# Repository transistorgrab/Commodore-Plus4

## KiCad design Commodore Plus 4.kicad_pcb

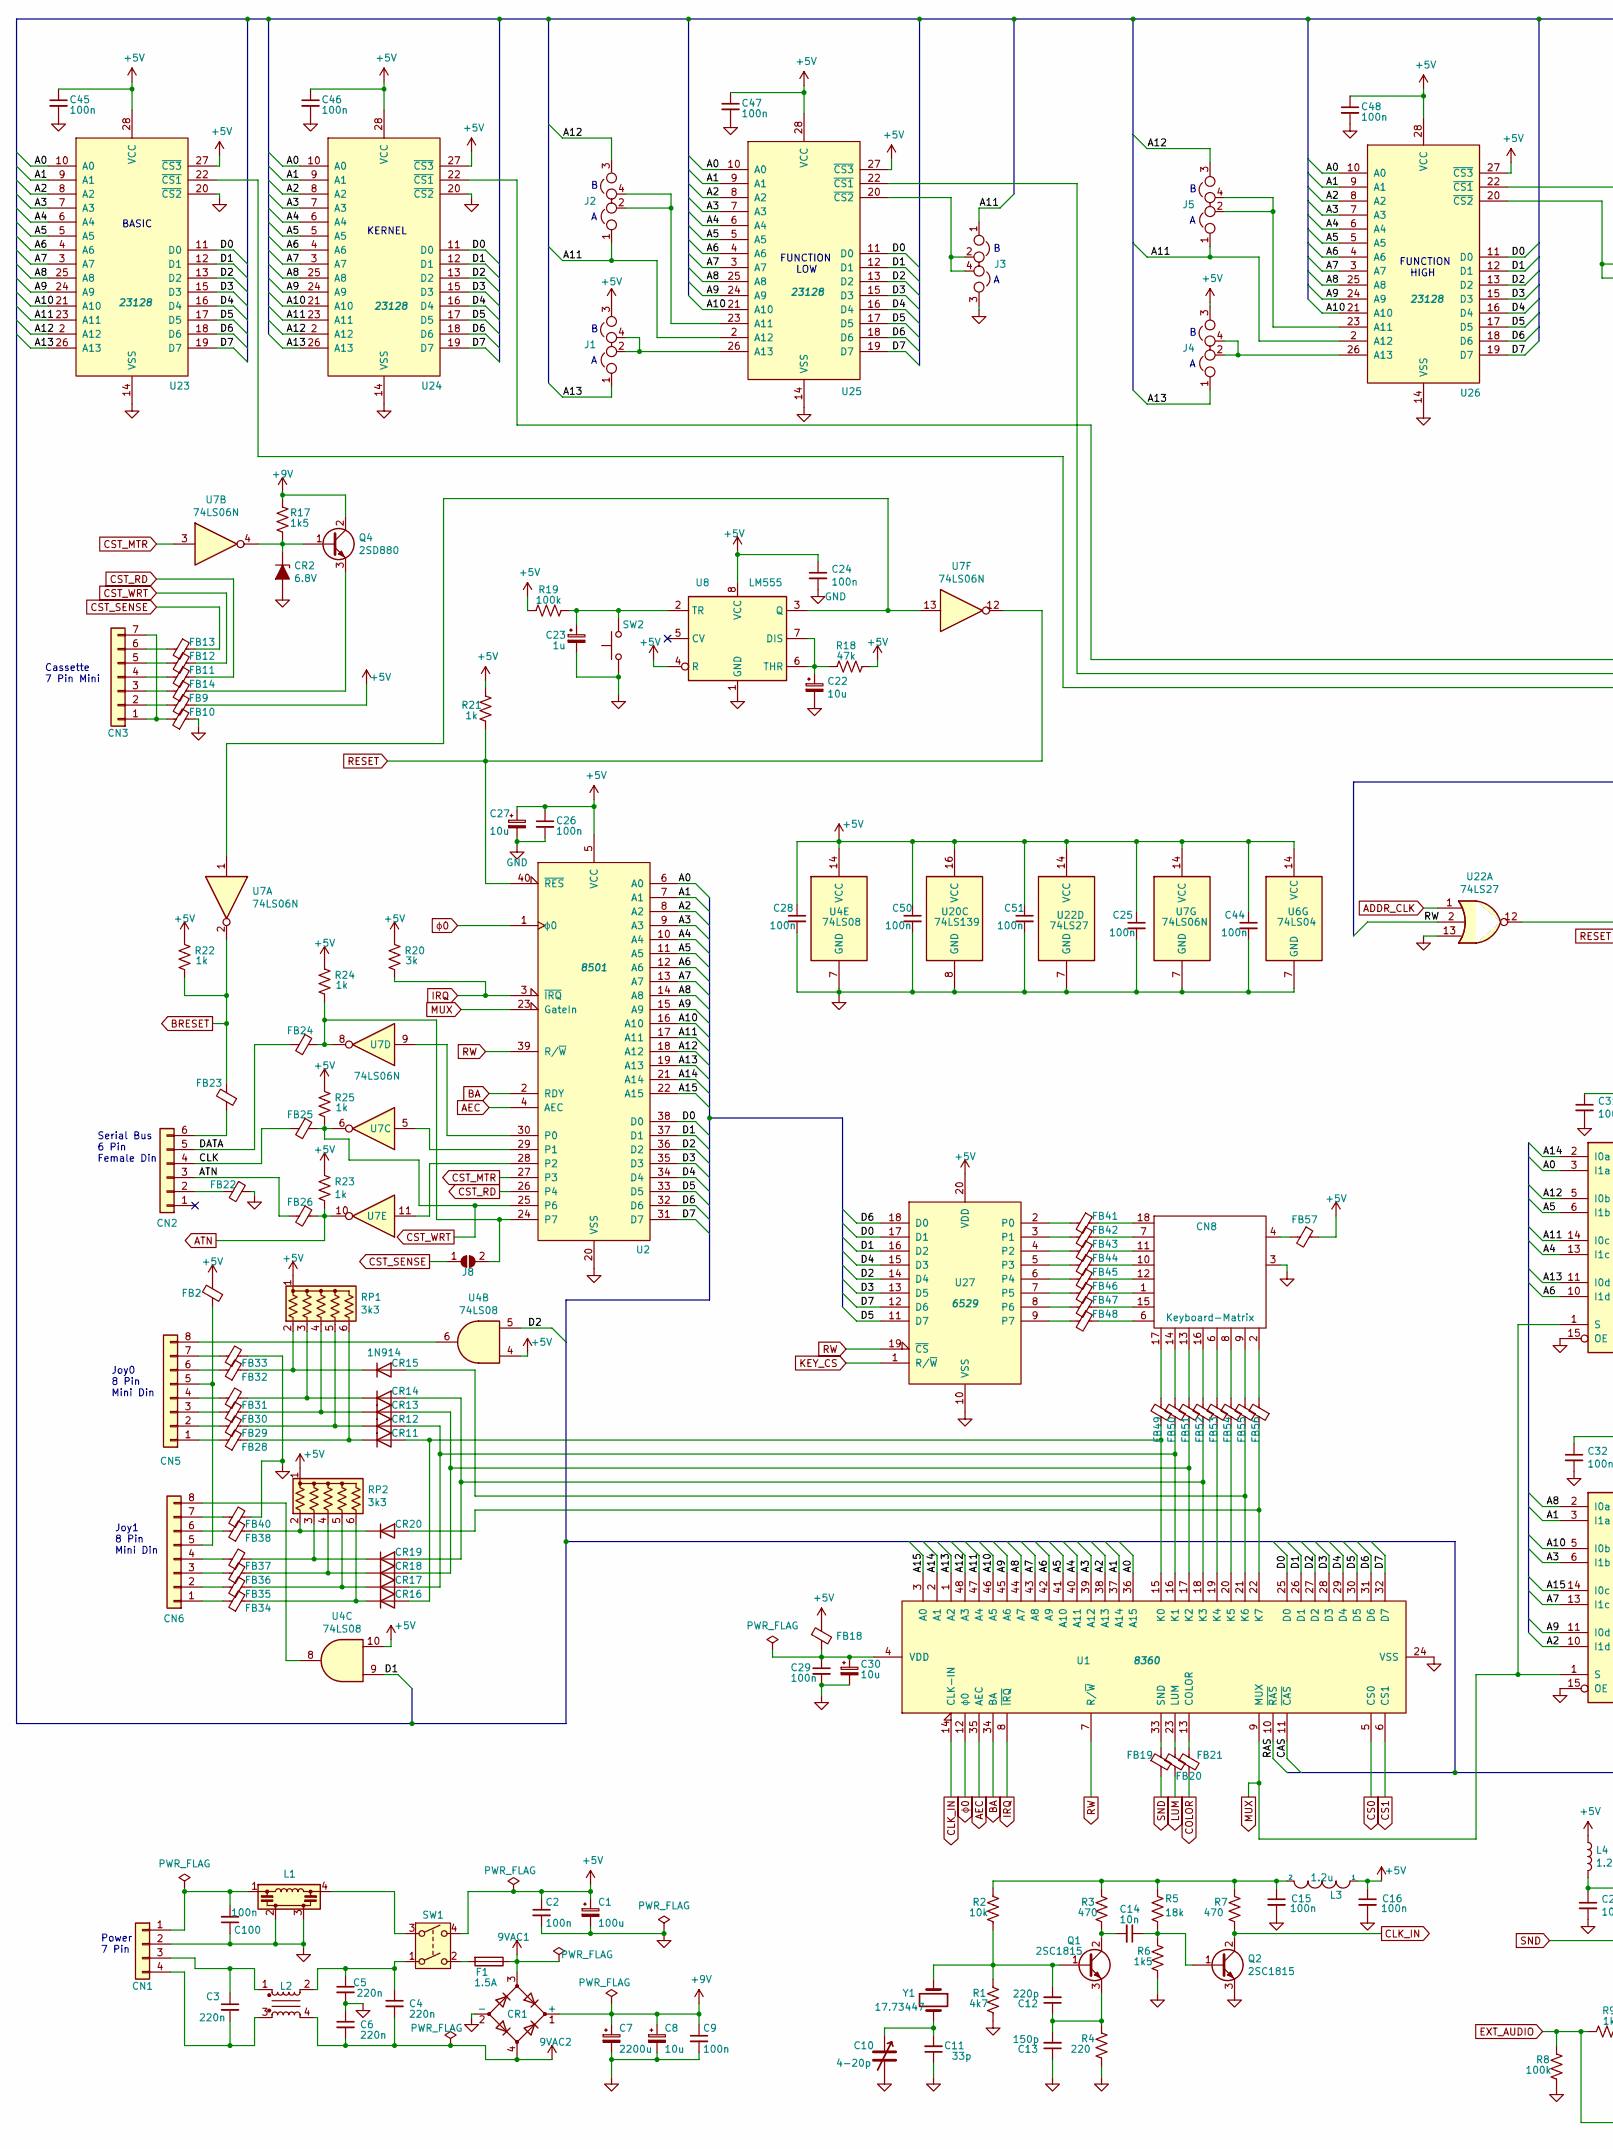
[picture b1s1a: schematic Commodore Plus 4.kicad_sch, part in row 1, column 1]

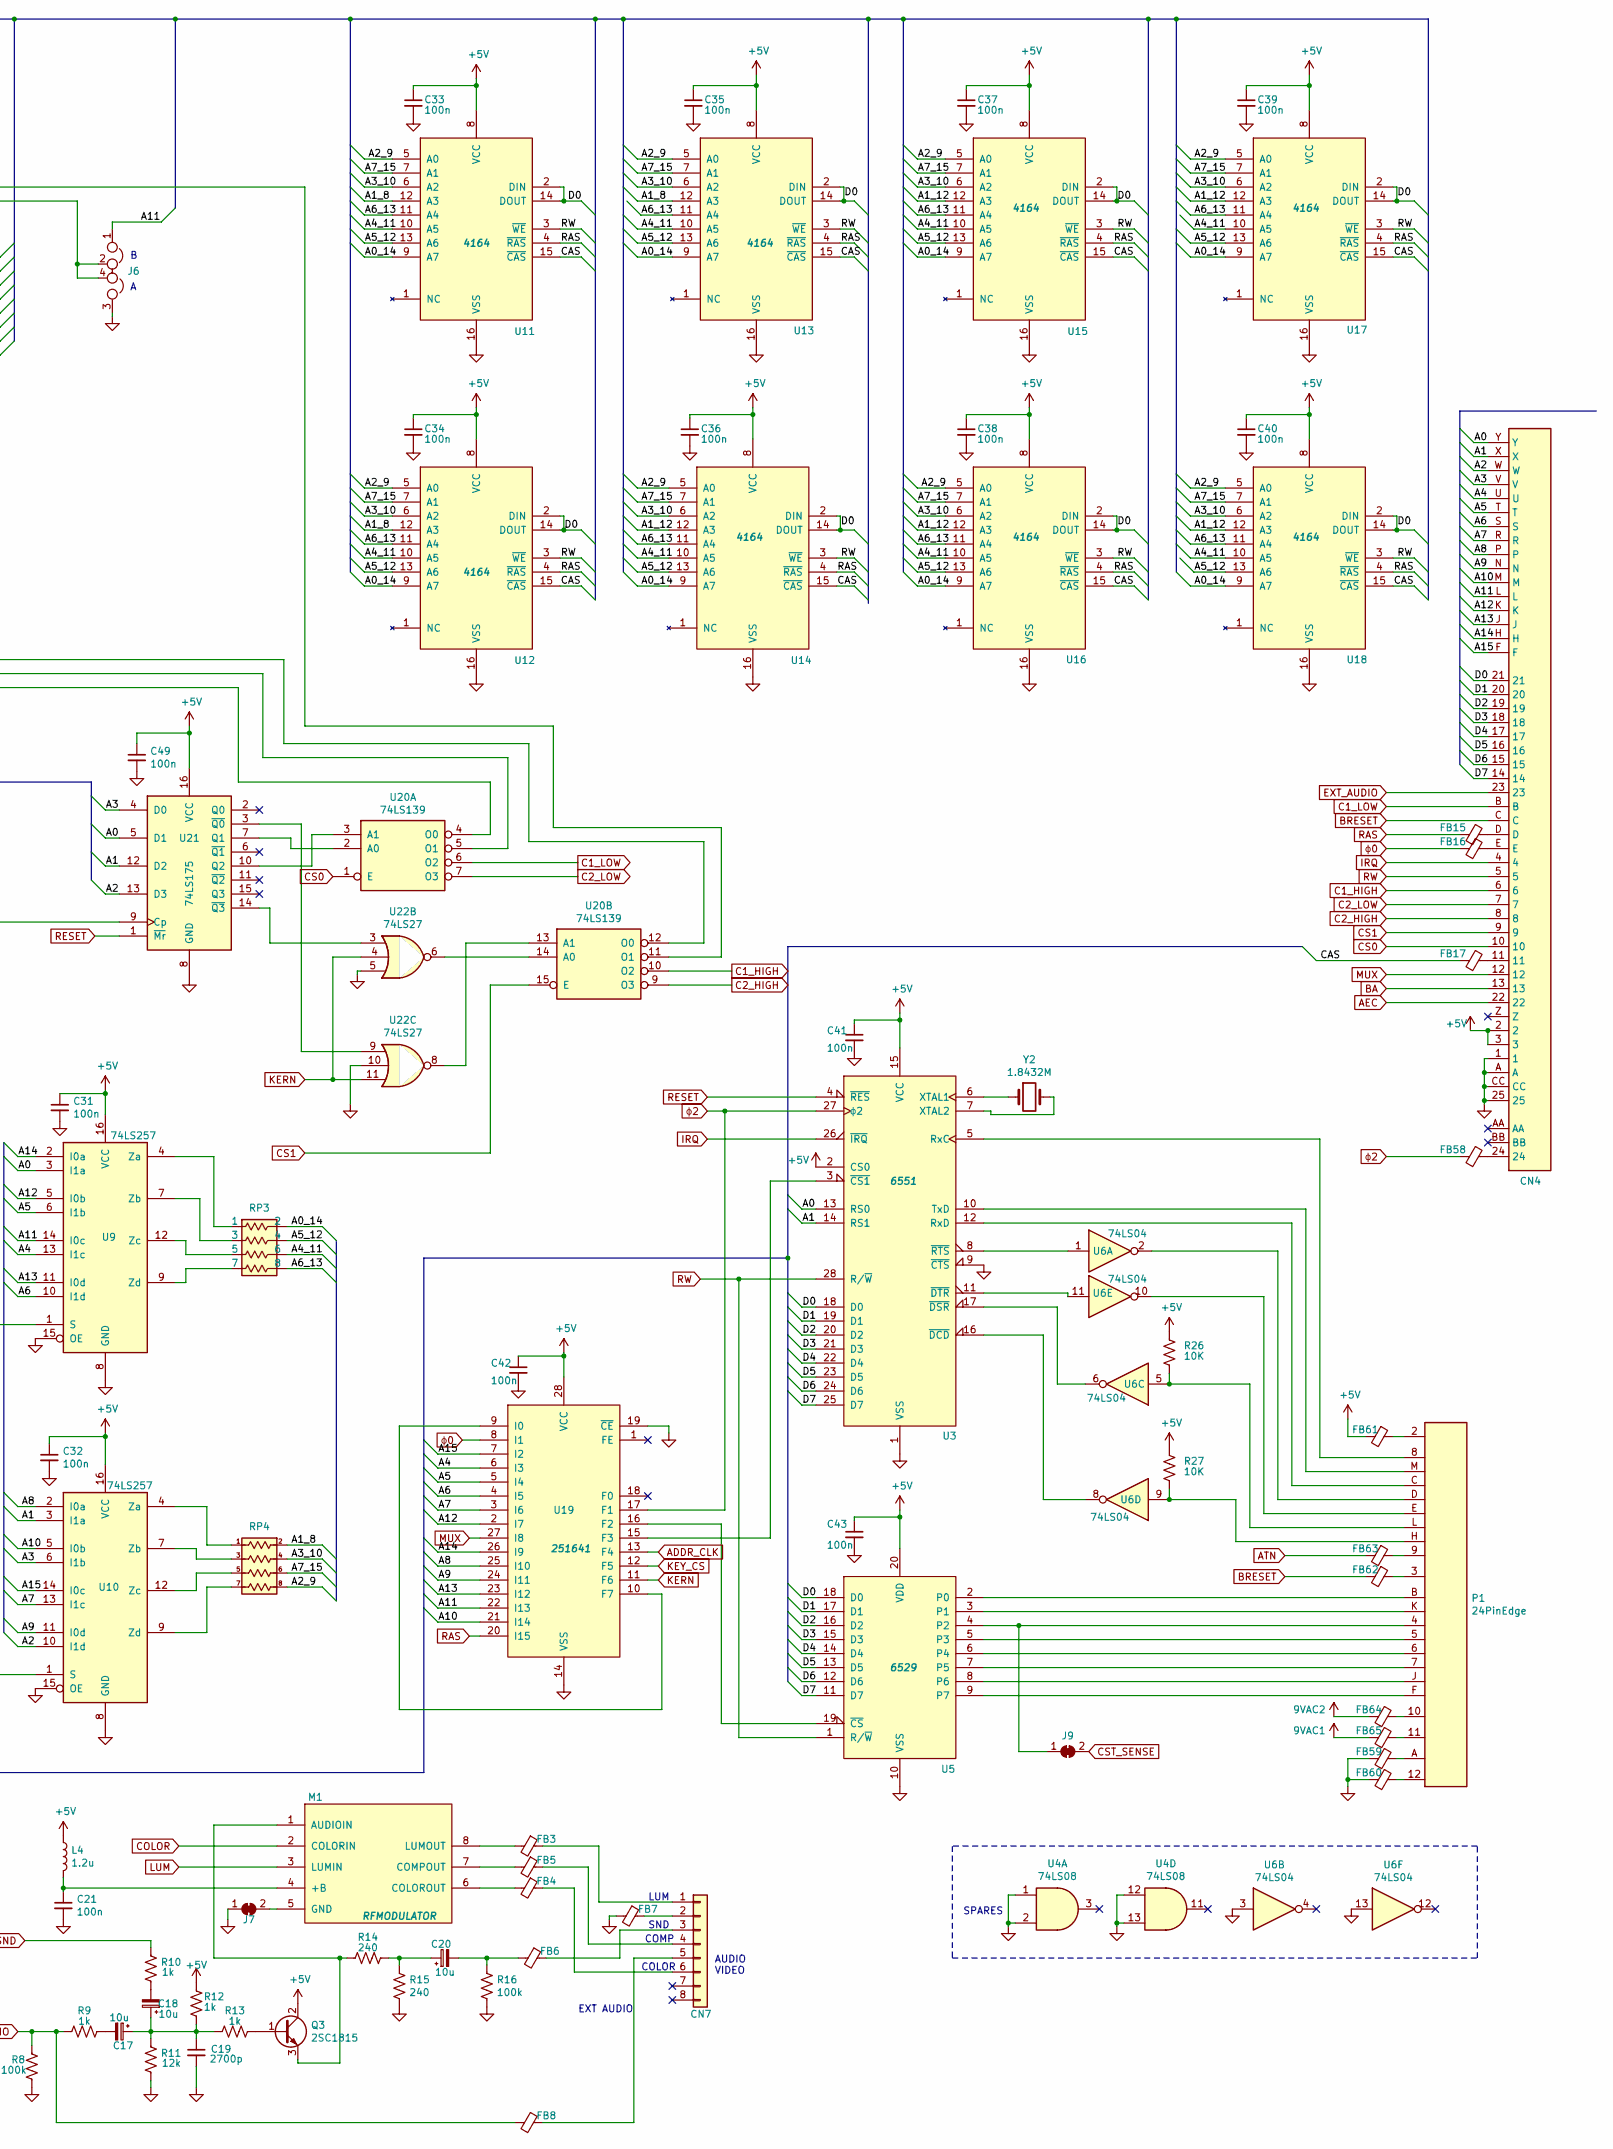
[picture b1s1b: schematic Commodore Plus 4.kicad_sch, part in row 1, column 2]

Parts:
C1: 100u; CP_Radial_D8.0mm_P3.50mm
C2, C9, C15, C16, C21, C24, C25, C26, C28, C29, C31, C32, C33, C34, C35, C36, C37, C38, C39, C41, C42, C43, C44, C45, C46, C47, C48, C49, C50, C51: 100n; C_Disc_D5.0mm_W2.5mm_P5.00mm
C3: 220n; C_Disc_D12.5mm_W5.0mm_P10.00mm
C4: 220n; Capacitor_D12.5mm_W5.0mm_P10.00mm
C5, C6: 220n; C_Disc_D5.0mm_W2.5mm_P5.00mm
C7: 2200u; CP_Axial_L40.0mm_D16.0mm_P48.00mm_Horizontal
C8, C20, C27: 10u; CP_Radial_D6.3mm_P2.50mm
C10: 4-20p; TrimCap_251029-02
C11: 33p; C_Disc_D5.0mm_W2.5mm_P5.00mm
C12: 220p; C_Disc_D5.0mm_W2.5mm_P5.00mm
C13: 150p; C_Disc_D5.0mm_W2.5mm_P5.00mm
C14: 10n; C_Disc_D5.0mm_W2.5mm_P5.00mm
C17, C18, C22, C30: 10u; C_Disc_10mm_6mm
C19: 2700p; C_Disc_D5.0mm_W2.5mm_P5.00mm
C23: 1u; CP_Radial_D6.3mm_P2.50mm
C40: 100n; C_Rect_L7.0mm_W2.5mm_P5.00mm
C100: 100n; C_Disc_D4.7mm_W2.5mm_P5.00mm
CN1: Conn_01x04; Connector_Power_4pin_251614_01
CN2: Conn_01x07; Connector_DIN_Female_6Pin_3rows
CN3: Conn_01x07; Connector_Mini-DIN_Female_7Pin_2rows
CN4: 50PinEdge; 50Pin_Edge_Connector
CN5, CN6: Conn_01x08; Connector_Mini-DIN_Female_8Pin_2rows
CN7: Conn_01x08; Connector_DIN_Female_8Pin_3rows
CN8: Keyboard-Matrix; Keyboard_Connector
CR1: D_Bridge_+-AA; Diode_Bridge_12.5x12.5
CR2: 6.8V; D_A-405_P12.70mm_Horizontal
CR11, CR12, CR13, CR14, CR15, CR16, CR17, CR18, CR19, CR20: 1N914; D_DO-35_SOD27_P12.70mm_Horizontal
F1: 1.5A; Fuseholder_Cylinder-6.3x32mm
FB2, FB3, FB4, FB5, FB6, FB7, FB8, FB9, FB10, FB11, FB12, FB13, FB14, FB22, FB23, FB24, FB25, FB26, FB28, FB29, FB30, FB31, FB32, FB33, FB34, FB35, FB36, FB37, FB38, FB40, FB59, FB61, FB62, FB63: Ferrite_Bead_Small; L_Axial_L7.0mm_D3.3mm_P5.08mm_Vertical
FB15, FB16, FB17, FB18, FB19, FB20, FB21, FB41, FB42, FB43, FB44, FB45, FB46, FB47, FB48, FB49, FB50, FB51, FB52, FB53, FB54, FB55, FB56, FB57, FB58, FB60, FB64, FB65: Ferrite_Bead_Small; Ferrite_Bead_L5.0mm_D3.6mm_P13.00mm_Horizontal
J1, J2, J3, J4, J5, J6: Jumper_NC_Dual; Jumper
J7, J9: SolderJumper_2_Bridged; SolderJumper-2_P1.3mm_Bridged_RoundedPad1.0x1.5mm
J8: SolderJumper_2_Open; SolderJumper-2_P1.3mm_Open_RoundedPad1.0x1.5mm
L1: EMI_Filter; EMI-Filter
L2: EMI_Filter_CommonMode; Noise_Filter
L3, L4: 1.2u; L_Axial_L10.0mm_D4.0mm_P15.5mm_Horizontal
M1: RFMODULATOR; RF_Modulator
P1: 24PinEdge; 24Pin_Edge
Q1, Q2, Q3: 2SC1815; TO-92L_Inline_Wide
Q4: 2SD880; TO-220-3_Vertical
R1: 4k7; Resistor_Horizontal
R2: 10k; Resistor_Horizontal
R3, R7: 470; Resistor_Horizontal
R4: 220; Resistor_Horizontal
R5: 18k; Resistor_Horizontal
R6, R17: 1k5; Resistor_Horizontal
R8, R16, R19: 100k; Resistor_Horizontal
R9, R10, R12, R13, R21, R22, R23, R24, R25: 1k; Resistor_Horizontal
R11: 12k; Resistor_Horizontal
R14, R15: 240; Resistor_Horizontal
R18: 47k; Resistor_Horizontal
R20: 3k; Resistor_Horizontal
R26, R27: 10K; Resistor_Horizontal
RP1, RP2: 3k3; R_Array_SIP6
RP3, RP4: Resistor-Network; R_Array_SIP8
SW1: SW_DPST; Switch-Rocker
SW2: SW_Push; Switch-Pushbutton
U1: 8360; DIP-48_W15.24mm
U2: 8501; DIP-40_W15.24mm
U3: 6551; DIP-28_W15.24mm
U4: 74LS08; DIP-14_W7.62mm
U5, U27: 6529; DIP-20_W7.62mm
U6: 74LS04; DIP-14_W7.62mm
U7: 74LS06N; DIP-14_W7.62mm
U8: LM555; DIP-8_W7.62mm
U9, U10: 74LS257; DIP-16_W7.62mm
U11, U12, U13, U14, U15, U16, U17, U18: 4164; DIP-16_W7.62mm
U19: 251641; DIP-28_W15.24mm
U20: 74LS139; DIP-16_W7.62mm
U21: 74LS175; DIP-16_W7.62mm
U22: 74LS27; DIP-14_W7.62mm
U23, U24, U25, U26: 23128; DIP-28_W15.24mm
Y1: 17.73447; Crystal_HC18-U_Horizontal
Y2: 1.8432M; Crystal_HC33-U_Horizontal

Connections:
9VAC1: CR1.3, F1.1, FB65.2
9VAC2: C4.2, C6.2, CR1.4, FB64.2, L2.4
+5V: C1.1, C2.1, C16.1, C24.1, C25.1, C26.1, C27.1, C28.1, C31.1, C32.1, C33.1, C34.1, C35.1, C36.1, C37.1, C38.1, C39.1, C40.1, C41.1, C42.1, C43.1, C44.1, C45.1, C46.1, C47.1, C48.1, C49.1, C50.1, C51.1, CN4.2, CN4.3, FB2.2, FB9.1, FB18.1, FB57.1, FB61.2, J1.3, J4.3, L3.1, L4.1, Q3.2 (C), R12.1, R18.1, R19.2, R20.1, R21.2, R22.1, R23.1, R24.1, R25.1, R26.1, R27.1, RP1.1 (common), RP2.1 (common), SW1.4, U2.5 (VCC), U3.2 (CS0), U3.15 (VCC), U4.4, U4.10, U4.14 (VCC), U5.20 (VDD), U6.14 (VCC), U7.14 (VCC), U8.4 (R), U8.8 (VCC), U9.16 (VCC), U10.16 (VCC), U11.8 (VCC), U12.8 (VCC), U13.8 (VCC), U14.8 (VCC), U15.8 (VCC), U16.8 (VCC), U17.8 (VCC), U18.8 (VCC), U19.28 (VCC), U20.16 (VCC), U21.16 (VCC), U22.14 (VCC), U23.27 (~CS3), U23.28 (VCC), U24.27 (~CS3), U24.28 (VCC), U25.27 (~CS3), U25.28 (VCC), U26.27 (~CS3), U26.28 (VCC), U27.20 (VDD)
+9V: C7.1, C8.1, C9.1, CR1.1 (+), Q4.2 (C), R17.1
/A0: CN4.Y, U1.36 (A15), U2.6 (A0), U3.13 (RS0), U9.3 (I1a), U21.5 (D1), U23.10 (A0), U24.10 (A0), U25.10 (A0), U26.10 (A0)
/A0_14: RP3.2, U11.9 (A7), U12.9 (A7), U13.9 (A7), U14.9 (A7), U15.9 (A7), U16.9 (A7), U17.9 (A7), U18.9 (A7)
/A1: CN4.X, U1.37 (A14), U2.7 (A1), U3.14 (RS1), U10.3 (I1a), U21.12 (D2), U23.9 (A1), U24.9 (A1), U25.9 (A1), U26.9 (A1)
/A1_8: RP4.2, U11.12 (A3), U12.12 (A3), U13.12 (A3)
/A1_12: U14.12 (A3), U15.12 (A3), U16.12 (A3), U17.12 (A3), U18.12 (A3)
/A2: CN4.W, U1.38 (A13), U2.8 (A2), U10.10 (I1d), U21.13 (D3), U23.8 (A2), U24.8 (A2), U25.8 (A2), U26.8 (A2)
/A2_9: RP4.8, U11.5 (A0), U12.5 (A0), U13.5 (A0), U14.5 (A0), U15.5 (A0), U16.5 (A0), U17.5 (A0), U18.5 (A0)
/A3: CN4.V, U1.39 (A12), U2.9 (A3), U10.6 (I1b), U21.4 (D0), U23.7 (A3), U24.7 (A3), U25.7 (A3), U26.7 (A3)
/A3_10: RP4.4, U11.6 (A2), U12.6 (A2), U13.6 (A2), U14.6 (A2), U15.6 (A2), U16.6 (A2), U17.6 (A2), U18.6 (A2)
/A4: CN4.U, U1.40 (A11), U2.10 (A4), U9.13 (I1c), U19.6 (I3), U23.6 (A4), U24.6 (A4), U25.6 (A4), U26.6 (A4)
/A4_11: RP3.6, U11.10 (A5), U12.10 (A5), U13.10 (A5), U14.10 (A5), U15.10 (A5), U16.10 (A5), U17.10 (A5), U18.10 (A5)
/A5: CN4.T, U1.41 (A10), U2.11 (A5), U9.6 (I1b), U19.5 (I4), U23.5 (A5), U24.5 (A5), U25.5 (A5), U26.5 (A5)
/A5_12: RP3.4, U11.13 (A6), U12.13 (A6), U13.13 (A6), U14.13 (A6), U15.13 (A6), U16.13 (A6), U17.13 (A6), U18.13 (A6)
/A6: CN4.S, U1.42 (A9), U2.12 (A6), U9.10 (I1d), U19.4 (I5), U23.4 (A6), U24.4 (A6), U25.4 (A6), U26.4 (A6)
/A6_13: RP3.8, U11.11 (A4), U12.11 (A4), U13.11 (A4), U14.11 (A4), U15.11 (A4), U16.11 (A4), U17.11 (A4), U18.11 (A4)
/A7: CN4.R, U1.43 (A8), U2.13 (A7), U10.13 (I1c), U19.3 (I6), U23.3 (A7), U24.3 (A7), U25.3 (A7), U26.3 (A7)
/A7_15: RP4.6, U11.7 (A1), U12.7 (A1), U13.7 (A1), U14.7 (A1), U15.7 (A1), U16.7 (A1), U17.7 (A1), U18.7 (A1)
/A8: CN4.P, U1.44 (A7), U2.14 (A8), U10.2 (I0a), U19.25 (I10), U23.25 (A8), U24.25 (A8), U25.25 (A8), U26.25 (A8)
/A9: CN4.N, U1.45 (A6), U2.15 (A9), U10.11 (I0d), U19.24 (I11), U23.24 (A9), U24.24 (A9), U25.24 (A9), U26.24 (A9)
/A10: CN4.M, U1.46 (A5), U2.16 (A10), U10.5 (I0b), U19.21 (I14), U23.21 (A10), U24.21 (A10), U25.21 (A10), U26.21 (A10)
/A11: CN4.L, J2.1, J3.1, J5.1, J6.1, U1.47 (A4), U2.17 (A11), U9.14 (I0c), U19.22 (I13), U23.23 (A11), U24.23 (A11), U25.2 (A12), U26.2 (A12)
/A12: CN4.K, J2.3, J5.3, U1.48 (A3), U2.18 (A12), U9.5 (I0b), U19.2 (I7), U23.2 (A12), U24.2 (A12)
/A13: CN4.J, J1.1, J4.1, U1.1 (A2), U2.19 (A13), U9.11 (I0d), U19.23 (I12), U23.26 (A13), U24.26 (A13)
/A14: CN4.H, U1.2 (A1), U2.21 (A14), U9.2 (I0a), U19.26 (I9)
/A15: CN4.F, U1.3 (A0), U2.22 (A15), U10.14 (I0c), U19.7 (I2)
/CAS: FB17.2, U1.11 (~CAS), U11.15 (~CAS), U12.15 (~CAS), U13.15 (~CAS), U14.15 (~CAS), U15.15 (~CAS), U16.15 (~CAS), U17.15 (~CAS), U18.15 (~CAS)
/CLK: CN2.4, FB25.2
/D0: CN4.21, U1.25 (D0), U2.38 (D0), U3.18 (D0), U5.18 (D0), U11.2 (DIN), U11.14 (DOUT), U12.2 (DIN), U12.14 (DOUT), U13.2 (DIN), U13.14 (DOUT), U14.2 (DIN), U14.14 (DOUT), U15.2 (DIN), U15.14 (DOUT), U16.2 (DIN), U16.14 (DOUT), U17.2 (DIN), U17.14 (DOUT), U18.2 (DIN), U18.14 (DOUT), U23.11 (D0), U24.11 (D0), U25.11 (D0), U26.11 (D0), U27.17 (D1)
/D1: CN4.20, U1.26 (D1), U2.37 (D1), U3.19 (D1), U4.9, U5.17 (D1), U23.12 (D1), U24.12 (D1), U25.12 (D1), U26.12 (D1), U27.16 (D2)
/D2: CN4.19, U1.27 (D2), U2.36 (D2), U3.20 (D2), U4.5, U5.16 (D2), U23.13 (D2), U24.13 (D2), U25.13 (D2), U26.13 (D2), U27.14 (D4)
/D3: CN4.18, U1.28 (D3), U2.35 (D3), U3.21 (D3), U5.15 (D3), U23.15 (D3), U24.15 (D3), U25.15 (D3), U26.15 (D3), U27.13 (D5)
/D4: CN4.17, U1.29 (D4), U2.34 (D4), U3.22 (D4), U5.14 (D4), U23.16 (D4), U24.16 (D4), U25.16 (D4), U26.16 (D4), U27.15 (D3)
/D5: CN4.16, U1.30 (D5), U2.33 (D5), U3.23 (D5), U5.13 (D5), U23.17 (D5), U24.17 (D5), U25.17 (D5), U26.17 (D5), U27.11 (D7)
/D6: CN4.15, U1.31 (D6), U2.32 (D6), U3.24 (D6), U5.12 (D6), U23.18 (D6), U24.18 (D6), U25.18 (D6), U26.18 (D6), U27.18 (D0)
/D7: CN4.14, U1.32 (D7), U2.31 (D7), U3.25 (D7), U5.11 (D7), U23.19 (D7), U24.19 (D7), U25.19 (D7), U26.19 (D7), U27.12 (D6)
/DATA: CN2.5, FB24.2
ADDR_CLK: U19.13 (F4), U22.1
AEC: CN4.22, U1.35 (AEC), U2.4 (AEC)
ATN: CN2.3, FB26.1, FB26.2, FB63.2, R23.2, U7.10
BA: CN4.13, U1.34 (BA), U2.2 (RDY)
BRESET: CN4.C, FB23.2, FB62.2, R22.2, U7.2
C1_HIGH: CN4.6, U20.10 (O2)
C1_LOW: CN4.B, U20.6 (O2)
C2_HIGH: CN4.8, U20.9 (O3)
C2_LOW: CN4.7, U20.7 (O3)
CLK_IN: Q2.2 (C), R7.2, U1.14 (CLK-IN)
COLOR: FB21.2, M1.2 (COLORIN)
CS0: CN4.10, U1.5 (CS0), U20.1 (E)
CS1: CN4.9, U1.6 (CS1), U20.15 (E)
CST_MTR: U2.27 (P3), U7.3
CST_RD: FB11.1, U2.26 (P4)
CST_SENSE: FB13.1, J8.1 (A), J9.2 (B)
CST_WRT: FB12.1, FB25.1, R25.2, U2.25 (P6), U7.6
EXT_AUDIO: CN4.23, FB8.2, R8.1, R9.2
GND: C1.2, C2.2, C5.2, C6.1, C7.2, C8.2, C9.2, C10.2, C11.1, C13.1, C15.2, C16.2, C19.2, C21.2, C22.2, C23.2, C24.2, C25.2, C26.2, C27.2, C28.2, C29.2, C30.2, C31.2, C32.2, C33.2, C34.2, C35.2, C36.2, C37.2, C38.2, C39.2, C40.2, C41.2, C42.2, C43.2, C44.2, C45.2, C46.2, C47.2, C48.2, C49.2, C50.2, C51.2, C100.1, CN1.2, CN4.1, CN4.25, CN4.A, CN4.CC, CN8.3, CR1.2 (-), CR2.2 (A), FB7.2, FB10.2, FB22.1, FB33.2, FB40.2, FB59.2, FB60.2, J3.3, J6.3, J7.1 (A), L1.2, L1.3, Q2.3 (E), R1.2, R4.2, R6.2, R8.2, R11.2, R15.2, R16.2, SW2.1, U1.24 (VSS), U2.20 (VSS), U3.1 (VSS), U3.9 (~CTS), U4.1, U4.2, U4.7 (GND), U4.12, U4.13, U5.10 (VSS), U6.3, U6.7 (GND), U6.13, U7.7 (GND), U8.1 (GND), U9.8 (GND), U9.15 (OE), U10.8 (GND), U10.15 (OE), U11.16 (VSS), U12.16 (VSS), U13.16 (VSS), U14.16 (VSS), U15.16 (VSS), U16.16 (VSS), U17.16 (VSS), U18.16 (VSS), U19.14 (VSS), U19.19 (~CE), U20.8 (GND), U21.8 (GND), U22.5, U22.7 (GND), U22.10, U22.13, U23.14 (VSS), U23.20 (~CS2), U24.14 (VSS), U24.20 (~CS2), U25.14 (VSS), U26.14 (VSS), U27.10 (VSS)
IRQ: CN4.4, R20.2, U1.8 (~IRQ), U2.3 (~IRQ), U3.26 (~IRQ)
KERN: U19.11 (F6), U22.4, U22.11
KEY_CS: U19.12 (F5), U27.1 (R/~W)
LUM: FB20.2, M1.3 (LUMIN)
MUX: CN4.12, U1.9 (MUX), U2.23 (GateIn), U9.1 (S), U10.1 (S), U19.27 (I8)
unnamed: C3.1, CN1.3, L2.1
unnamed: C3.2, CN1.4, L2.3
unnamed: C4.1, C5.1, L2.2, SW1.1
unnamed: C10.1, C11.2, Y1.2
unnamed: C12.1, C13.2, Q1.3 (E), R4.1
unnamed: C12.2, Q1.1 (B), R1.1, R2.2, Y1.1
unnamed: C14.1, Q2.1 (B), R5.2, R6.1
unnamed: C14.2, Q1.2 (C), R3.2
unnamed: C15.1, L3.2, R2.1, R3.1, R5.1, R7.1
unnamed: C17.1, C18.1, C19.1, R11.1, R12.2, R13.2
unnamed: C17.2, R9.1
unnamed: C18.2, R10.2
unnamed: C20.1, R14.1, R15.1
unnamed: C20.2, FB6.2, R16.1
unnamed: C21.1, L4.2, M1.4 (+B)
unnamed: C22.1, R18.2, U8.6 (THR), U8.7 (DIS)
unnamed: C23.1, R19.1, SW2.2, U8.2 (TR)
unnamed: C29.1, C30.1, FB18.2, U1.4 (VDD)
unnamed: C100.2, CN1.1, L1.1
unnamed: CN2.2, FB22.2
unnamed: CN2.6, FB23.1
unnamed: CN3.1, CN3.7, FB10.1
unnamed: CN3.2, FB9.2
unnamed: CN3.3, FB14.2
unnamed: CN3.4, FB11.2
unnamed: CN3.5, FB12.2
unnamed: CN3.6, FB13.2
unnamed: CN4.11, FB17.1
unnamed: CN4.24, FB58.1
unnamed: CN4.D, FB15.1
unnamed: CN4.E, FB16.1
unnamed: CN5.1, FB28.1
unnamed: CN5.2, FB29.1
unnamed: CN5.3, FB30.1
unnamed: CN5.4, FB31.1
unnamed: CN5.5, CN6.5, FB2.1
unnamed: CN5.6, FB32.1
unnamed: CN5.7, FB33.1
unnamed: CN5.8, U4.6
unnamed: CN6.1, FB34.1
unnamed: CN6.2, FB35.1
unnamed: CN6.3, FB36.1
unnamed: CN6.4, FB37.1
unnamed: CN6.6, FB38.1
unnamed: CN6.7, FB40.1
unnamed: CN6.8, U4.8
unnamed: CN7.1, FB3.1
unnamed: CN7.2, FB7.1
unnamed: CN7.3, FB6.1
unnamed: CN7.4, FB5.1
unnamed: CN7.5, FB8.1
unnamed: CN7.6, FB4.1
unnamed: CN8.1, FB46.1
unnamed: CN8.2, FB56.2
unnamed: CN8.4, FB57.2
unnamed: CN8.7, FB42.1
unnamed: CN8.8, FB54.2
unnamed: CN8.9, FB55.2
unnamed: CN8.10, FB44.1
unnamed: CN8.11, FB43.1
unnamed: CN8.12, FB45.1
unnamed: CN8.13, FB51.2
unnamed: CN8.14, FB50.2
unnamed: CN8.15, FB47.1
unnamed: CN8.16, FB52.2
unnamed: CN8.17, FB49.2
unnamed: CN8.18, FB41.1
unnamed: CR2.1 (K), Q4.1 (B), R17.2, U7.4
unnamed: CR11.1 (K), FB28.2, RP1.6 (R5)
unnamed: CR11.2 (A), CR16.2 (A), FB49.1, U1.15 (K0)
unnamed: CR12.1 (K), FB29.2, RP1.5 (R4)
unnamed: CR12.2 (A), CR17.2 (A), FB50.1, U1.16 (K1)
unnamed: CR13.1 (K), FB30.2, RP1.4 (R3)
unnamed: CR13.2 (A), CR18.2 (A), FB51.1, U1.17 (K2)
unnamed: CR14.1 (K), FB31.2, RP1.3 (R2)
unnamed: CR14.2 (A), CR19.2 (A), FB52.1, U1.18 (K3)
unnamed: CR15.1 (K), FB32.2, RP1.2 (R1)
unnamed: CR15.2 (A), FB55.1, U1.21 (K6)
unnamed: CR16.1 (K), FB34.2, RP2.6 (R5)
unnamed: CR17.1 (K), FB35.2, RP2.5 (R4)
unnamed: CR18.1 (K), FB36.2, RP2.4 (R3)
unnamed: CR19.1 (K), FB37.2, RP2.3 (R2)
unnamed: CR20.1 (K), FB38.2, RP2.2 (R1)
unnamed: CR20.2 (A), FB56.1, U1.22 (K7)
unnamed: F1.2, SW1.2
unnamed: FB3.2, M1.8 (LUMOUT)
unnamed: FB4.2, M1.6 (COLOROUT)
unnamed: FB5.2, M1.7 (COMPOUT)
unnamed: FB14.1, Q4.3 (E)
unnamed: FB19.1, U1.33 (SND)
unnamed: FB20.1, U1.23 (LUM)
unnamed: FB21.1, U1.13 (COLOR)
unnamed: FB24.1, J8.2 (B), R24.2, U2.24 (P7), U7.8
unnamed: FB41.2, U27.2 (P0)
unnamed: FB42.2, U27.3 (P1)
unnamed: FB43.2, U27.4 (P2)
unnamed: FB44.2, U27.5 (P3)
unnamed: FB45.2, U27.6 (P4)
unnamed: FB46.2, U27.7 (P5)
unnamed: FB47.2, U27.8 (P6)
unnamed: FB48.2, U27.9 (P7)
unnamed: FB53.1, U1.19 (K4)
unnamed: FB54.1, U1.20 (K5)
unnamed: FB59.1, P1.A
unnamed: FB60.1, P1.12
unnamed: FB61.1, P1.2
unnamed: FB62.1, P1.3
unnamed: FB63.1, P1.9
unnamed: FB64.1, P1.10
unnamed: FB65.1, P1.11
unnamed: J1.2, J1.4, U25.26 (A13)
unnamed: J2.2, J2.4, U25.23 (A11)
unnamed: J3.2, J3.4, U25.20 (~CS2)
unnamed: J4.2, J4.4, U26.26 (A13)
unnamed: J5.2, J5.4, U26.23 (A11)
unnamed: J6.2, J6.4, U26.20 (~CS2)
unnamed: J7.2 (B), M1.5 (GND)
unnamed: J9.1 (A), P1.4, U5.4 (P2)
unnamed: L1.4, SW1.3
unnamed: M1.1 (AUDIOIN), Q3.3 (E), R14.2
unnamed: P1.5, U5.5 (P3)
unnamed: P1.6, U5.6 (P4)
unnamed: P1.7, U5.7 (P5)
unnamed: P1.8, U3.5 (RxC)
unnamed: P1.B, U5.2 (P0)
unnamed: P1.C, U3.12 (RxD)
unnamed: P1.D, U6.2
unnamed: P1.E, U6.10
unnamed: P1.F, U5.9 (P7)
unnamed: P1.H, R27.2, U6.9
unnamed: P1.J, U5.8 (P6)
unnamed: P1.K, U5.3 (P1)
unnamed: P1.L, R26.2, U6.5
unnamed: P1.M, U3.10 (TxD)
unnamed: Q3.1 (B), R13.1
unnamed: RP3.1, U9.4 (Za)
unnamed: RP3.3, U9.7 (Zb)
unnamed: RP3.5, U9.12 (Zc)
unnamed: RP3.7, U9.9 (Zd)
unnamed: RP4.1, U10.4 (Za)
unnamed: RP4.3, U10.7 (Zb)
unnamed: RP4.5, U10.12 (Zc)
unnamed: RP4.7, U10.9 (Zd)
unnamed: U2.28 (P2), U7.11
unnamed: U2.29 (P1), U7.5
unnamed: U2.30 (P0), U7.9
unnamed: U3.6 (XTAL1), Y2.1
unnamed: U3.7 (XTAL2), Y2.2
unnamed: U3.8 (~RTS), U6.1
unnamed: U3.11 (~DTR), U6.11
unnamed: U3.16 (~DCD), U6.8
unnamed: U3.17 (~DSR), U6.6
unnamed: U7.1, U7.13, U8.3 (Q)
unnamed: U19.9 (I0), U19.10 (F7)
unnamed: U3.3 (~CS1), U19.15 (F3)
unnamed: U5.19 (~CS), U19.16 (F2)
unnamed: U20.2 (A0), U21.7 (Q1)
unnamed: U20.3 (A1), U21.10 (Q2)
unnamed: U20.4 (O0), U23.22 (~CS1)
unnamed: U20.5 (O1), U25.22 (~CS1)
unnamed: U20.11 (O1), U26.22 (~CS1)
unnamed: U20.12 (O0), U24.22 (~CS1)
unnamed: U20.13 (A1), U22.8
unnamed: U20.14 (A0), U22.6
unnamed: U21.3 (~Q0), U22.9
unnamed: U21.9 (Cp), U22.12
unnamed: U21.14 (~Q3), U22.3
RAS: FB15.2, U1.10 (~RAS), U11.4 (~RAS), U12.4 (~RAS), U13.4 (~RAS), U14.4 (~RAS), U15.4 (~RAS), U16.4 (~RAS), U17.4 (~RAS), U18.4 (~RAS), U19.20 (I15)
RESET: R21.1, U2.40 (~RES), U3.4 (~RES), U7.12, U21.1 (~Mr)
RW: CN4.5, U1.7 (R/~W), U2.39 (R/~W), U3.28 (R/~W), U5.1 (R/~W), U11.3 (~WE), U12.3 (~WE), U13.3 (~WE), U14.3 (~WE), U15.3 (~WE), U16.3 (~WE), U17.3 (~WE), U18.3 (~WE), U22.2, U27.19 (~CS)
SND: FB19.2, R10.1
ϕ0: FB16.2, U1.12 (ϕ0), U2.1 (ϕ0), U19.8 (I1)
ϕ2: FB58.2, U3.27 (ϕ2), U19.17 (F1)

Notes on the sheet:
Power 7 Pin
FUNCTION LOW
COMP
Cassette 7 Pin Mini
KERNEL
LUM
FUNCTION HIGH
Joy0 8 Pin Mini Din
SND
Joy1 8 Pin Mini Din
EXT AUDIO
SPARES
AUDIO VIDEO
BASIC
Serial Bus 6 Pin Female Din
COLOR

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
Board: 2 copper layers, 216 parts (0 on the bottom side), 238 nets, no tracks yet.

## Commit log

2024-02-18 updates files for Kicad 8, some cleanup on libs and schematic
